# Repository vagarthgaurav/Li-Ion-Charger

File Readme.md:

# USB-C PD Li-ion Charger

This project is a standalone Li ion Charger for singel cell 18650 batteries. 
It uses a switching regulator to be as efficient as possible. 
The board is powered by USB C Power Delivery.

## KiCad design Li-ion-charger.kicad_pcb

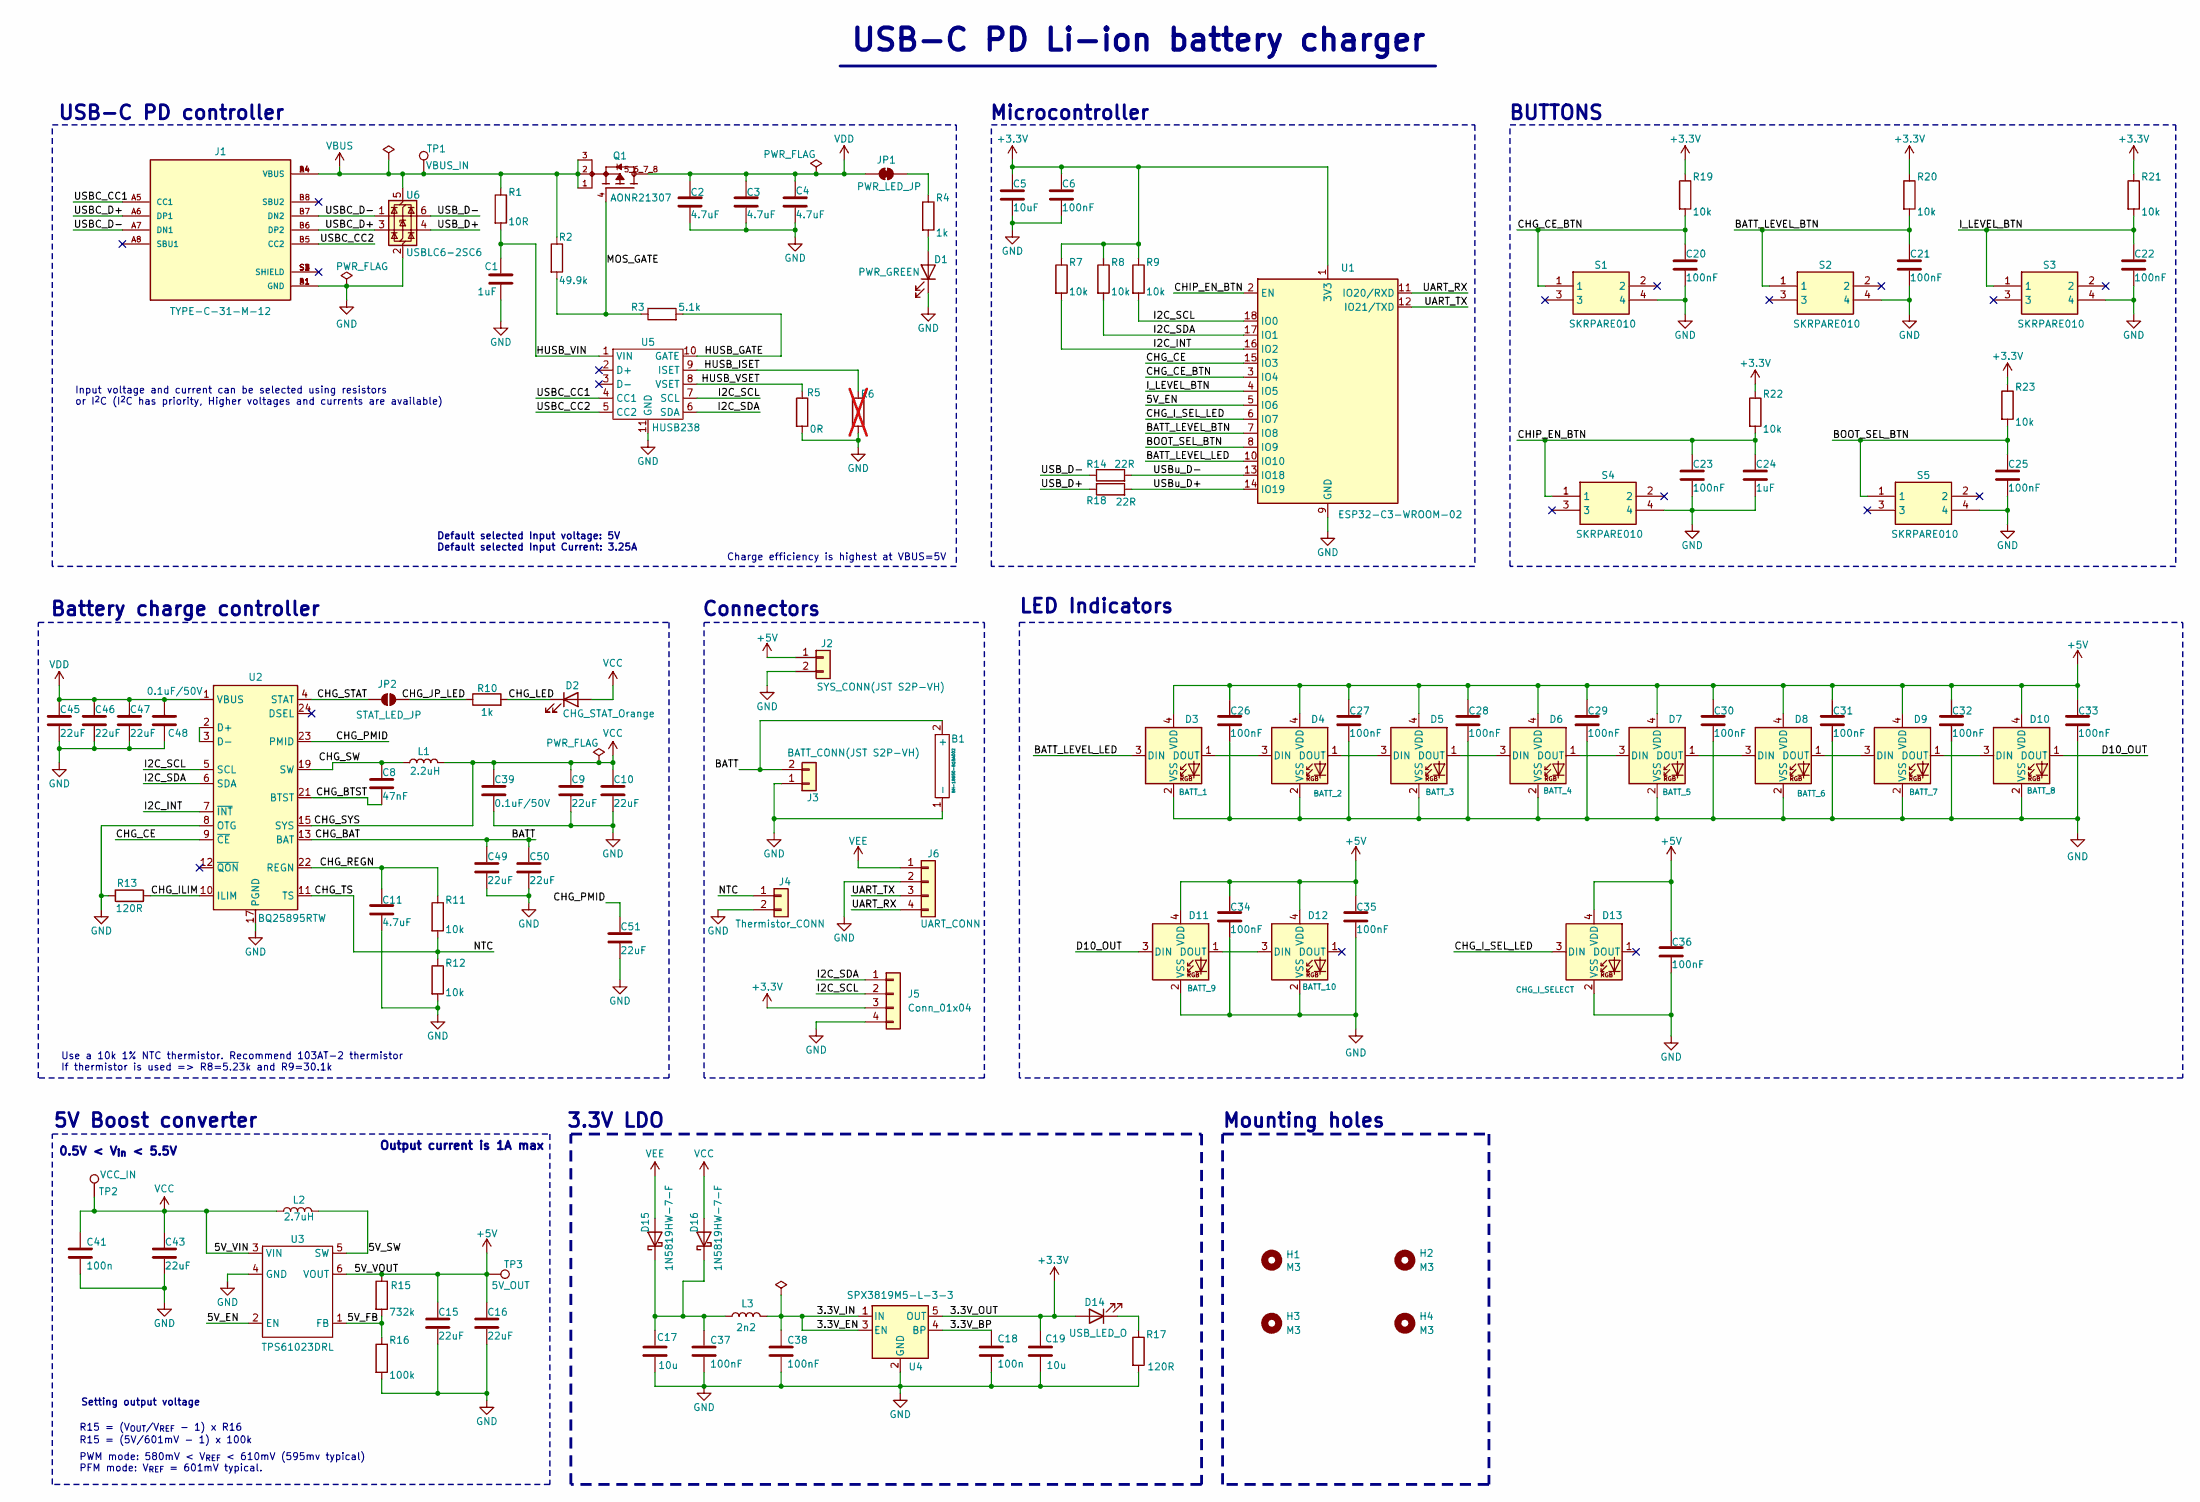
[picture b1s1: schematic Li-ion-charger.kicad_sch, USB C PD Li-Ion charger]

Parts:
B1: BH-18650-B1BA002
C1, C24: 1uF; C_0805_2012Metric
C2, C3, C4, C11: 4.7uF; C_0805_2012Metric
C5: 10uF; C_0603_1608Metric
C6, C20, C21, C22, C23, C25, C26, C27, C28, C29, C30, C31, C32, C33, C34, C35, C36, C37, C38: 100nF; C_0402_1005Metric
C8: 47nF; C_0402_1005Metric
C9, C10, C15, C16, C43, C45, C46, C47, C49, C50, C51: 22uF; C_0805_2012Metric
C17, C19: 10u; C_0603_1608Metric
C18, C41: 100n; C_0402_1005Metric
C39, C48: 0.1uF/50V; C_0603_1608Metric
D1: PWR_GREEN; LED_0402_1005Metric
D2: CHG_STAT_Orange; LED_0402_1005Metric
D3: BATT_1; LED_WS2812B-2020_PLCC4_2.0x2.0mm
D4: BATT_2; LED_WS2812B-2020_PLCC4_2.0x2.0mm
D5: BATT_3; LED_WS2812B-2020_PLCC4_2.0x2.0mm
D6: BATT_4; LED_WS2812B-2020_PLCC4_2.0x2.0mm
D7: BATT_5; LED_WS2812B-2020_PLCC4_2.0x2.0mm
D8: BATT_6; LED_WS2812B-2020_PLCC4_2.0x2.0mm
D9: BATT_7; LED_WS2812B-2020_PLCC4_2.0x2.0mm
D10: BATT_8; LED_WS2812B-2020_PLCC4_2.0x2.0mm
D11: BATT_9; LED_WS2812B-2020_PLCC4_2.0x2.0mm
D12: BATT_10; LED_WS2812B-2020_PLCC4_2.0x2.0mm
D13: CHG_I_SELECT; LED_WS2812B-2020_PLCC4_2.0x2.0mm
D14: USB_LED_O; LED_0402_1005Metric
D15, D16: 1N5819HW-7-F; D_SOD-123
H1, H2, H3, H4: M3; MountingHole_3mm
J1: TYPE-C-31-M-12; HRO_TYPE-C-31-M-12; PARTREV 2020.12.08
J2: SYS_CONN(JST S2P-VH); JST_VH_S2P-VH_1x02_P3.96mm_Horizontal
J3: BATT_CONN(JST S2P-VH); JST_VH_S2P-VH_1x02_P3.96mm_Horizontal
J4: Thermistor_CONN; PinHeader_1x02_P2.54mm_Vertical
J5: Conn_01x04; PinHeader_1x04_P2.54mm_Vertical
J6: UART_CONN; PinHeader_1x04_P2.54mm_Vertical
JP1: PWR_LED_JP; SolderJumper-2_P1.3mm_Bridged_RoundedPad1.0x1.5mm
JP2: STAT_LED_JP; SolderJumper-2_P1.3mm_Open_TrianglePad1.0x1.5mm
L1: 2.2uH; SPM6530
L2: 2.7uH; L_Changjiang_FNR6045S
L3: 2n2; L_0402_1005Metric
Q1: AONR21307; aonr21307; PARTREV 1.1
R1: 10R; R_0805_2012Metric
R2: 49.9k; R_0805_2012Metric
R3: 5.1k; R_0805_2012Metric
R4, R10: 1k; R_0402_1005Metric
R5: 0R; R_0402_1005Metric
R6: 0R; R_0402_1005Metric; not fitted
R7, R8, R9, R11, R12, R19, R20, R21, R22, R23: 10k; R_0402_1005Metric
R13, R17: 120R; R_0402_1005Metric
R14, R18: 22R; R_0402_1005Metric
R15: 732k; R_0402_1005Metric
R16: 100k; R_0402_1005Metric
S1, S2, S3, S4, S5: SKRPARE010; Mouser Part Number 688-SKRPARE010
TP1: VBUS_IN; TestPoint_Pad_D1.5mm
TP2: VCC_IN; TestPoint_Pad_D1.5mm
TP3: 5V_OUT; TestPoint_Pad_D1.5mm
U1: ESP32-C3-WROOM-02
U2: BQ25895RTW; Texas_RTW_WQFN-24-1EP_4x4mm_P0.5mm_EP2.7x2.7mm_ThermalVias
U3: TPS61023DRL; SOTFL50P160X60-6N
U4: SPX3819M5-L-3-3; SOT-23-5
U5: HUSB238; DFN-10-1EP_3x3mm_P0.5mm_EP1.65x2.38mm_ThermalVias
U6: USBLC6-2SC6; SOT-23-6

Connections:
+3.3V: C5.1, C6.1, C19.1, D14.2 (A), J5.3, R7.1, R8.1, R9.1, R19.1, R20.1, R21.1, R22.1, R23.1, U1.1 (3V3), U4.5 (OUT)
+5V: C15.1, C16.1, C26.1, C27.1, C28.1, C29.1, C30.1, C31.1, C32.1, C33.1, C34.1, C35.1, C36.1, D3.4 (VDD), D4.4 (VDD), D5.4 (VDD), D6.4 (VDD), D7.4 (VDD), D8.4 (VDD), D9.4 (VDD), D10.4 (VDD), D11.4 (VDD), D12.4 (VDD), D13.4 (VDD), J2.1, R15.1, TP3.1, U3.6 (VOUT)
/3.3V_BP: C18.1, U4.4 (BP)
/3.3V_EN: C38.1, L3.2, U4.1 (IN), U4.3 (EN)
/5V_EN: U1.5 (IO6), U3.2 (EN)
/5V_FB: R15.2, R16.1, U3.1 (FB)
/5V_SW: L2.2, U3.5 (SW)
/BATT: B1.2 (+), C49.1, C50.1, J3.2, U2.13 (BAT), U2.14 (BAT)
/BATT_LEVEL_BTN: C21.1, R20.2, S2.1, U1.7 (IO8)
/BATT_LEVEL_LED: D3.3 (DIN), U1.10 (IO10)
/BOOT_SEL_BTN: C25.1, R23.2, S5.1, U1.8 (IO9)
/CHG_BTST: C8.2, U2.21 (BTST)
/CHG_CE: U1.15 (IO3), U2.9 (~CE)
/CHG_CE_BTN: C20.1, R19.2, S1.1, U1.3 (IO4)
/CHG_ILIM: R13.2, U2.10 (ILIM)
/CHG_I_SEL_LED: D13.3 (DIN), U1.6 (IO7)
/CHG_JP_LED: JP2.2 (B), R10.1
/CHG_LED: D2.1 (K), R10.2
/CHG_PMID: C51.1, U2.23 (PMID)
/CHG_REGN: C11.1, R11.1, U2.22 (REGN)
/CHG_STAT: JP2.1 (A), U2.4 (STAT)
/CHG_SW: C8.1, L1.1, U2.19 (SW), U2.20 (SW)
/CHG_TS: J4.1, R11.2, R12.1, U2.11 (TS)
/CHIP_EN_BTN: C23.1, C24.1, R22.2, S4.1, U1.2 (EN)
/D10_OUT: D10.1 (DOUT), D11.3 (DIN)
/HUSB_GATE: R3.2, U5.10 (GATE)
/HUSB_ISET: R6.2, U5.9 (ISET)
/HUSB_VIN: C1.1, R1.2, U5.1 (VIN)
/HUSB_VSET: R5.1, U5.8 (VSET)
/I2C_INT: R7.2, U1.16 (IO2), U2.7 (~INT)
/I2C_SCL: J5.2, R9.2, U1.18 (IO0), U2.5 (SCL), U5.7 (SCL)
/I2C_SDA: J5.1, R8.2, U1.17 (IO1), U2.6 (SDA), U5.6 (SDA)
/I_LEVEL_BTN: C22.1, R21.2, S3.1, U1.4 (IO5)
/MOS_GATE: Q1.4, R2.2, R3.1
/UART_RX: J6.4, U1.11 (IO20/RXD)
/UART_TX: J6.3, U1.12 (IO21/TXD)
/USBC_CC1: J1.A5 (CC1), U5.4 (CC1)
/USBC_CC2: J1.B5 (CC2), U5.5 (CC2)
/USBC_D+: J1.A6 (DP1), J1.B6 (DP2), U6.3 (I/O2)
/USBC_D-: J1.A7 (DN1), J1.B7 (DN2), U6.1 (I/O1)
/USB_D+: R18.1, U6.4 (I/O2)
/USB_D-: R14.1, U6.6 (I/O1)
/USBu_D+: R18.2, U1.14 (IO19)
/USBu_D-: R14.2, U1.13 (IO18)
GND: B1.1 (-), C1.2, C2.2, C3.2, C4.2, C5.2, C6.2, C9.2, C10.2, C11.2, C15.2, C16.2, C17.2, C18.2, C19.2, C20.2, C21.2, C22.2, C23.2, C24.2, C25.2, C26.2, C27.2, C28.2, C29.2, C30.2, C31.2, C32.2, C33.2, C34.2, C35.2, C36.2, C37.2, C38.2, C39.2, C41.2, C43.2, C45.2, C46.2, C47.2, C48.2, C49.2, C50.2, C51.2, D1.1 (K), D3.2 (VSS), D4.2 (VSS), D5.2 (VSS), D6.2 (VSS), D7.2 (VSS), D8.2 (VSS), D9.2 (VSS), D10.2 (VSS), D11.2 (VSS), D12.2 (VSS), D13.2 (VSS), J1.A1 (GND), J1.B1 (GND), J2.2, J3.1, J4.2, J5.4, J6.2, R5.2, R6.1, R12.2, R13.1, R16.2, R17.2, S1.4, S2.4, S3.4, S4.4, S5.4, U1.9 (GND), U1.19 (GND), U2.8 (OTG), U2.17 (PGND), U2.18 (PGND), U2.25 (PGND), U3.4 (GND), U4.2 (GND), U5.11 (GND), U6.2 (GND)
unnamed: D1.2 (A), R4.2
unnamed: D3.1 (DOUT), D4.3 (DIN)
unnamed: D4.1 (DOUT), D5.3 (DIN)
unnamed: D5.1 (DOUT), D6.3 (DIN)
unnamed: D6.1 (DOUT), D7.3 (DIN)
unnamed: D7.1 (DOUT), D8.3 (DIN)
unnamed: D8.1 (DOUT), D9.3 (DIN)
unnamed: D9.1 (DOUT), D10.3 (DIN)
unnamed: D11.1 (DOUT), D12.3 (DIN)
unnamed: D14.1 (K), R17.1
unnamed: C17.1, C37.1, D15.1 (K), D16.1 (K), L3.1
unnamed: JP1.2 (B), R4.1
unnamed: U2.2 (D+), U2.3 (D-)
VBUS: J1.A4 (VBUS), J1.B4 (VBUS), Q1.1, Q1.2, Q1.3, R1.1, R2.1, TP1.1, U6.5 (VBUS)
VCC: C9.1, C10.1, C39.1, C41.1, C43.1, D2.2 (A), D16.2 (A), L1.2, L2.1, TP2.1, U2.15 (SYS), U2.16 (SYS), U3.3 (VIN)
VDD: C2.1, C3.1, C4.1, C45.1, C46.1, C47.1, C48.1, JP1.1 (A), Q1.5_6_7_8, U2.1 (VBUS)
VEE: D15.2 (A), J6.1

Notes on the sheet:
Battery charge controller
5V Boost converter
Use a 10k 1% NTC thermistor. Recommend 103AT-2 thermistor If thermistor is used => R8=5.23k and R9=30.1k
Charge efficiency is highest at VBUS=5V
BUTTONS
3.3V LDO
Default selected Input voltage: 5V Default selected Input Current: 3.25A
Connectors
Input voltage and current can be selected using resistors or I^{2}C (I^{2}C has priority, Higher voltages and currents are available)
Setting output voltage
R15 = (5V/601mV - 1) x 100k
USB-C PD Li-ion battery charger
0.5V < V_{in} < 5.5V
Output current is 1A max
Mounting holes
Microcontroller
R15 = (V_{OUT}/V_{REF} - 1) x R16
PWM mode: 580mV < V_{REF} < 610mV (595mv typical) PFM mode: V_{REF} = 601mV typical.
USB-C PD controller
LED Indicators

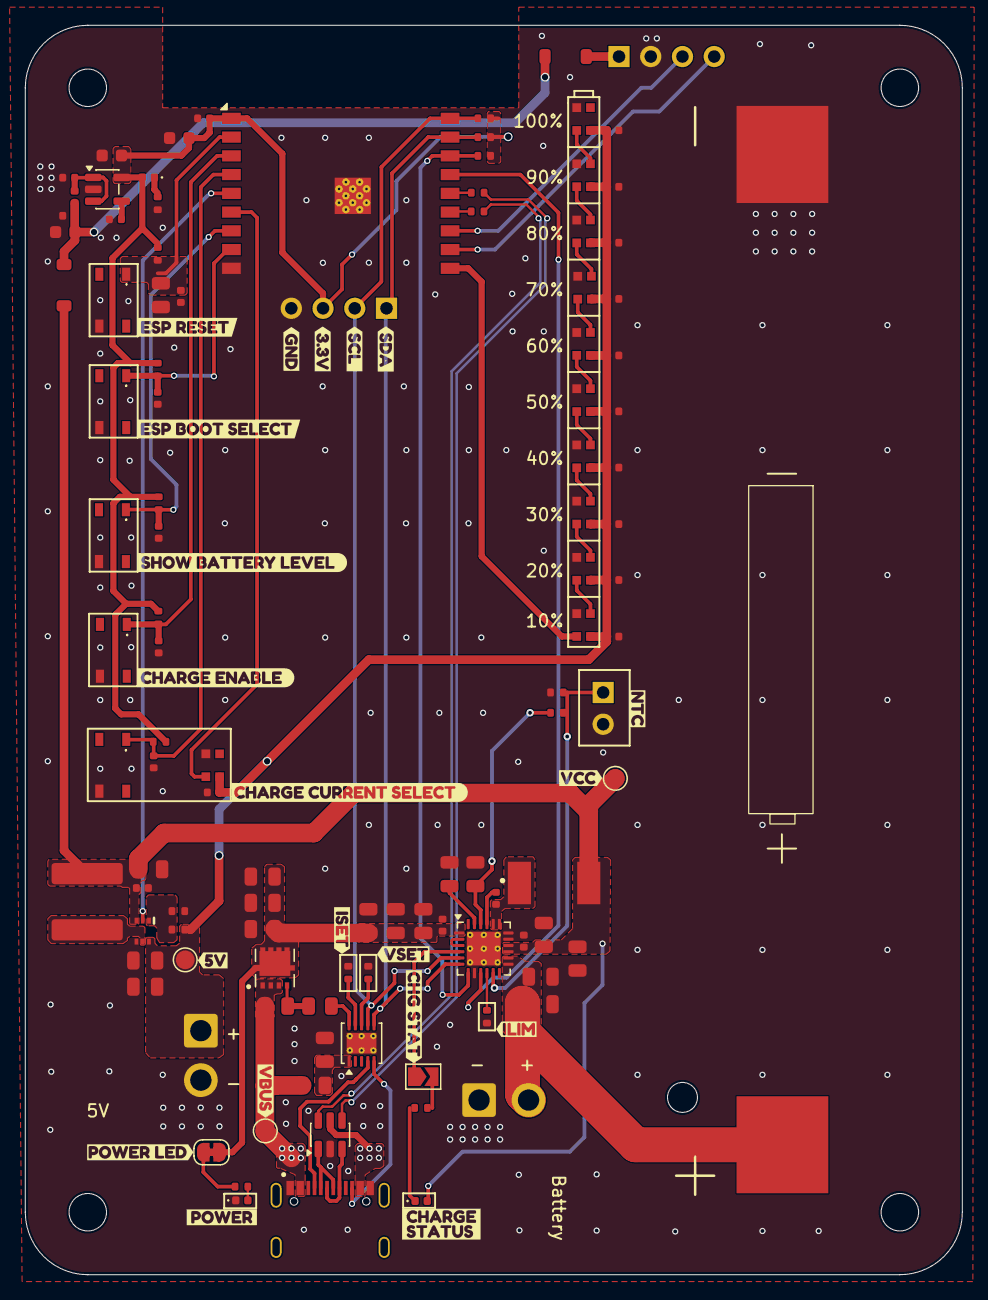
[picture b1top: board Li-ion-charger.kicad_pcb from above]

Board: 4 copper layers, 75.0 x 100.0 mm, 134 parts (0 on the bottom side), 62 nets.

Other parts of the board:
kibuzzard-6914ED2A: G***; kibuzzard-6914ED2A
kibuzzard-69087ACC: G***; kibuzzard-69087ACC
kibuzzard-69087B0B: G***; kibuzzard-69087B0B
kibuzzard-69087B9F: G***; kibuzzard-69087B9F
kibuzzard-69087B55: G***; kibuzzard-69087B55
kibuzzard-69087BEB: G***; kibuzzard-69087BEB
kibuzzard-69087C9F: G***; kibuzzard-69087C9F
kibuzzard-69087C39: G***; kibuzzard-69087C39
kibuzzard-69087DFE: G***; kibuzzard-69087DFE
kibuzzard-69087E63: G***; kibuzzard-69087E63
kibuzzard-69087EC1: G***; kibuzzard-69087EC1
kibuzzard-69087EF8: G***; kibuzzard-69087EF8
kibuzzard-69087F54: G***; kibuzzard-69087F54
kibuzzard-690665AE: G***; kibuzzard-690665AE
kibuzzard-690667D4: G***; kibuzzard-690667D4
kibuzzard-6906673D: G***; kibuzzard-6906673D
kibuzzard-6908973F: G***; kibuzzard-6908973F
kibuzzard-69066962: G***; kibuzzard-69066962
kibuzzard-69066992: G***; kibuzzard-69066992
kibuzzard-69089838: G***; kibuzzard-69089838

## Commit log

2025-11-11 Add Readme
2025-11-13 Improve filtering
2026-01-05 feat: Add schematic pdf
2026-01-05 doc: Add 3D render to readme
